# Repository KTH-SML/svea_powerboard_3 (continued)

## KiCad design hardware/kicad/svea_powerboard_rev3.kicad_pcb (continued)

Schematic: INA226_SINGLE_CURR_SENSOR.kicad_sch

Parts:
C89: 1u; C_0603_1608Metric; Manufacturer Part CL10B105KB8NQNC; LCSC Part Name 1uF ±10% 50V
C90: 100n; C_0603_1608Metric; Manufacturer Part CC0603KRX7R9BB104; LCSC Part Name 100nF ±10% 50V
NT18, NT19: NetTie_2; NetTie-2_SMD_Pad0.2mm
R2501: 100k; R_0402_1005Metric; LCSC C25741
U72: INA226AIDGSR; VSSOP-10_3x3mm_P0.5mm; Manufacturer Part INA226AIDGSR; LCSC Part Name 高侧/低侧测量双向电流/功率监视器，具有I2C兼容接口

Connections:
+3V3: C89.1, C90.2, R2501.2, U72.6 (VS+); also elsewhere on the board
/Battery System/ESC FET/OUT+: NT19.1; also elsewhere on the board
/Battery System/INA226_SINGLE_CURR_SENSOR_ESC/VIN_N: NT18.2, U72.9 (VIN-)
/Battery System/INA226_SINGLE_CURR_SENSOR_ESC/VIN_P: NT19.2, U72.8 (VBUS), U72.10 (VIN+)
Current/INA226-ESC-0x4E/ALERT: R2501.1, U72.3 (Alert); also elsewhere on the board
GND: C89.2, C90.1, U72.7 (GND); also elsewhere on the board
SCL_SLOW: U72.1 (A1), U72.5 (SCL); also elsewhere on the board
SDA_SLOW: U72.2 (A0), U72.4 (SDA); also elsewhere on the board
VCC_ESC: NT18.1; also elsewhere on the board

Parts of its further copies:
C126: 1u; C_0603_1608Metric; Manufacturer Part CL10B105KB8NQNC; LCSC Part Name 1uF ±10% 50V
C127: 100n; C_0603_1608Metric; Manufacturer Part CC0603KRX7R9BB104; LCSC Part Name 100nF ±10% 50V
NT28, NT29: NetTie_2; NetTie-2_SMD_Pad0.2mm
R3301: 100k; R_0402_1005Metric; LCSC C25741
U81: INA226AIDGSR; VSSOP-10_3x3mm_P0.5mm; Manufacturer Part INA226AIDGSR; LCSC Part Name 高侧/低侧测量双向电流/功率监视器，具有I2C兼容接口

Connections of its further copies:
+3V3: C126.1, C127.2, R3301.2, U81.6 (VS+); also elsewhere on the board
/Battery System/INA226_SINGLE_CURR_SENSOR_SERVO/VIN_N: NT28.2, U81.9 (VIN-)
/Battery System/INA226_SINGLE_CURR_SENSOR_SERVO/VIN_P: NT29.2, U81.8 (VBUS), U81.10 (VIN+)
/Battery System/servo_vcc: NT29.1; also elsewhere on the board
Current/INA226-SERVO-0x4F/ALERT: R3301.1, U81.3 (Alert); also elsewhere on the board
GND: C126.2, C127.1, U81.7 (GND); also elsewhere on the board
SCL_SLOW: U81.1 (A1), U81.2 (A0), U81.5 (SCL); also elsewhere on the board
SDA_SLOW: U81.4 (SDA); also elsewhere on the board
servo_vcc_indicator: NT28.1; also elsewhere on the board

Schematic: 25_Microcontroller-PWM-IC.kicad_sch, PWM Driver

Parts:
C117: 100n; C_0603_1608Metric; Manufacturer Part CC0603KRX7R9BB104; LCSC Part Name 100nF ±10% 50V
C118: 1u; C_0603_1608Metric; Manufacturer Part CL10A105KB8NNNC; LCSC Part Name 1uF ±10% 50V
R181, R182, R183, R184, R186, R188: 10k; R_0402_1005Metric; Manufacturer Part 0402WGF1002TCE; LCSC Part Name 10kΩ ±1% 62.5mW 厚膜电阻
U78: PCA9685PW,118; TSSOP-28_4.4x9.7mm_P0.65mm; Manufacturer Part PCA9685PW,118; LCSC Part Name 16通道、12位PWM Fm+ I2C总线LED控制器
U3201: EXB2HV102JV; Manufacturer Part EXB2HV102JV; LCSC C713453

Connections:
+3V3: C117.2, C118.2, R186.2, U78.24 (A5), U78.28 (VDD); also elsewhere on the board
/Battery System/ServoConnectors/Extra1: U3201.11; also elsewhere on the board
/Battery System/ServoConnectors/Extra2: U3201.10; also elsewhere on the board
/Battery System/ServoConnectors/FrontDiff: U3201.14; also elsewhere on the board
/Battery System/ServoConnectors/Gear: U3201.12; also elsewhere on the board
/Battery System/ServoConnectors/RearDiff: U3201.13; also elsewhere on the board
/Battery System/ServoConnectors/Steering: U3201.15; also elsewhere on the board
/Battery System/ServoConnectors/Throttle: U3201.16; also elsewhere on the board
GND: C117.1, C118.1, R181.1, R182.1, R183.1, R184.1, R188.2, U78.14 (VSS), U78.25 (EXTCLK); also elsewhere on the board
unnamed: R186.1, U78.1 (A0)
unnamed: R181.2, U78.2 (A1)
unnamed: R182.2, U78.3 (A2)
unnamed: R183.2, U78.4 (A3)
unnamed: R184.2, U78.5 (A4)
unnamed: U78.6 (LED0), U3201.1
unnamed: U78.7 (LED1), U3201.2
unnamed: U78.8 (LED2), U3201.3
unnamed: U78.9 (LED3), U3201.4
unnamed: U78.10 (LED4), U3201.5
unnamed: U78.11 (LED5), U3201.6
unnamed: U78.12 (LED6), U3201.7
unnamed: R188.1, U78.23 (OE#)
SCL_SLOW: U78.26 (SCL); also elsewhere on the board
SDA_SLOW: U78.27 (SDA); also elsewhere on the board

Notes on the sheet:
0x61

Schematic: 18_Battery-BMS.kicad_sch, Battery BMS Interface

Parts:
C114: 100n; C_0603_1608Metric; Manufacturer Part TCC0603X7R104K500CT; LCSC Part Name 100nF ±10% 50V
C115: 100p; C_0402_1005Metric; Manufacturer Part FCC0402N101J500AT; LCSC Part Name 100pF ±5% 50V
C116: 2.2u; C_0603_1608Metric; LCSC C23630
C119: 470n; C_0603_1608Metric; Manufacturer Part 0603B474K500NT; LCSC Part Name 470nF ±10% 50V
C120: 1u; C_0603_1608Metric; Manufacturer Part CGA0603X5R105K500JT; LCSC Part Name 1uF ±10% 50V
C3501, C3502, C3503, C3505: 220n; C_0402_1005Metric; lcsc C531424
C3504: 100p; C_0402_1005Metric; LCSC C281751
D21, D22: BAT46W-7-F; D_SOD-123; Manufacturer Part BAT46W-7-F; LCSC Part Name 电压:100V 电流:150mA
JP3401: SolderJumper_2_Open; SolderJumper-2_P1.3mm_Open_TrianglePad1.0x1.5mm
JP3402: SolderJumper_2_Bridged; SolderJumper-2_P1.3mm_Bridged_Pad1.0x1.5mm
LED9: XL-1608UOC-06; LED_0603_1608Metric; Manufacturer Part XL-1608UOC-06; LCSC C965800
Q3: L2N7002SLLT1G; SOT-23; Manufacturer Part L2N7002SLLT1G; LCSC Part Name 1个N沟道 耐压:60V 电流:380mA
R20: 220; R_0603_1608Metric; LCSC C22962
R21, R3506: 100k; R_0402_1005Metric; LCSC C25741
R175: 20; R_0603_1608Metric; Manufacturer Part FRC0603F20R0TS; LCSC Part Name 20Ω ±1% 100mW 厚膜电阻
R185, R187: 100; R_0603_1608Metric; Manufacturer Part 0603WAF1000T5E; LCSC Part Name 100Ω ±1% 100mW 厚膜电阻
R190: 100; R_1206_3216Metric; Manufacturer Part 1206W4F1000T5E; LCSC Part Name 100Ω ±1% 250mW 厚膜电阻
R3501, R3502, R3503: 20; R_0603_1608Metric; LCSC C22950
R3504, R3505, R3508: 10k; R_0402_1005Metric; LCSC C25744
R3507: 82k; R_0402_1005Metric; LCSC C4142
U80: BQ7694202pBR; TQFP-48_7x7mm_P0.5mm; Manufacturer Part BQ7694202PFBR; LCSC Part Name 适用于锂离子、锂聚合物和磷酸铁锂电池组的3节至10节高精度串联电池监控器和保护器

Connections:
/Battery System/Battery BMS Interface/ALERT_PULLUP: R20.1, R3508.2; also elsewhere on the board
/Battery System/Battery BMS Interface/BAL-CELL-2: R3502.1; also elsewhere on the board
/Battery System/Battery BMS Interface/BAL-CELL-TOP: JP3402.2 (B), R3501.1; also elsewhere on the board
/Battery System/Battery BMS Interface/BAL_CELL_BOT+: R3503.1; also elsewhere on the board
/Battery System/Battery BMS Interface/BAL_CELL_BOT-: R175.1; also elsewhere on the board
/Battery System/Battery BMS Interface/BQ-BAT: JP3401.1 (A); also elsewhere on the board
/Battery System/Battery BMS Interface/CHG: U80.45 (CHG); also elsewhere on the board
/Battery System/Battery BMS Interface/DSG: U80.43 (DSG); also elsewhere on the board
/Battery System/Battery BMS Interface/PCHG: U80.40 (PCHG)
/Battery System/Battery BMS Interface/PDSG: U80.39 (PDSG); also elsewhere on the board
/Battery System/Battery BMS Interface/REG18: C116.1, U80.24 (REG18); also elsewhere on the board
/Battery System/Battery BMS Interface/TS1: U80.21 (TS1)
/Battery System/Battery BMS Interface/TS2: U80.22 (TS2); also elsewhere on the board
/Battery System/Battery BMS Interface/TS3: U80.23 (TS3)
/Battery System/Battery BMS Interface/VC0: C3505.2, R175.2, U80.16 (VC0)
/Battery System/Battery BMS Interface/VC1: C3501.1, C3502.2, R3503.2, U80.15 (VC1)
/Battery System/Battery BMS Interface/VC3: C3502.1, C3503.2, R3502.2, U80.2 (VC9), U80.4 (VC8), U80.6 (VC7), U80.8 (VC6), U80.10 (VC5), U80.12 (VC4), U80.13 (VC3), U80.14 (VC2)
/Battery System/Battery BMS Interface/VC4: C3503.1, R3501.2, U80.48 (VC10)
/Battery System/Battery BMS Interface/VSS: C116.2, C120.1, C3501.2, C3504.2, C3505.1, R3506.2, R3507.2, U80.17 (VSS), U80.36 (REGIN), U80.37 (BREG); also elsewhere on the board
/Battery System/Battery Power Path/bat_shunt_N: R187.1; also elsewhere on the board
/Battery System/Battery Power Path/bat_shunt_P: R185.1; also elsewhere on the board
BQ/ALERT: Q3.1 (G), R21.1, R3508.1, U80.25 (ALERT)
BQ/ALERT/LED: LED9.2 (A), Q3.3 (D); also elsewhere on the board
BQ/RST-SHUT: R3506.1, U80.33 (RST_SHUT); also elsewhere on the board
GND: Q3.2 (S), R21.2; also elsewhere on the board
unnamed: D21.1, D22.1, R190.2
unnamed: D21.2, JP3401.2 (B)
unnamed: D22.2, JP3402.1 (A)
unnamed: LED9.1 (K), R20.2
unnamed: C119.2, C120.2, C3504.1, R190.1, U80.47 (BAT)
unnamed: C119.1, U80.46 (CP1)
unnamed: R3505.1, U80.41 (LD)
unnamed: R3504.1, U80.42 (PACK)
unnamed: R3507.1, U80.34 (REG2), U80.35 (REG1)
unnamed: C114.1, C115.2, R187.2, U80.20 (SRN)
unnamed: C114.2, C115.1, R185.2, U80.18 (SRP)
PACK+: R3504.2, R3505.2; also elsewhere on the board
SCL_SLOW: U80.26 (SCL); also elsewhere on the board
SDA_SLOW: U80.27 (SDA); also elsewhere on the board

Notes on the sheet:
4.5mA
0x08
Power from the big main bat connector
Everything here should be VSS

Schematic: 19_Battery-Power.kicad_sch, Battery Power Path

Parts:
C122, C123, C124, C125, C128, C129: 100n; C_0603_1608Metric; Manufacturer Part CL10B104KC8NNNC; LCSC Part Name 100nF ±10% 100V
D23, D28, D30: MMSZ5246B-7-F; D_SOD-123; Manufacturer Part MMSZ5246B-7-F; LCSC Part Name 独立式 耐压:16V 电流:0.1uA@12V
D24: MMSZ5267BT1G; D_SOD-123; Manufacturer Part MMSZ5267BT1G; LCSC Part Name 独立式 耐压:75V 电流:0.1uA@56V
D25, D27: BAT46W-7-F; D_SOD-123; Manufacturer Part BAT46W-7-F; LCSC Part Name 电压:100V 电流:150mA
D26: MMSZ5246B_R1_00001; D_SOD-123; Manufacturer Part MMSZ5246B_R1_00001; LCSC Part Name 独立式 耐压:16V 电流:0.1uA@12V
D29: BZT52C5V1S-7-F; D_SOD-323; Manufacturer Part BZT52C5V1S-7-F; LCSC Part Name 独立式 耐压:5.1V 电流:1uA
D31: BAT46W; D_SOD-123; Manufacturer Part BAT46W; LCSC Part Name 电压:100V 电流:150mA
NT30, NT31: NetTie_2; NetTie-2_SMD_Pad0.2mm
Q13, Q14: IPT012N08N5(TOKMAS); Infineon_PG-HSOF-8-1; Manufacturer Part IPT012N08N5(TOKMAS); LCSC Part Name 1个N沟道 耐压:85V 电流:300A
Q15: ZXMP10A17GTA; SOT-223; Manufacturer Part ZXMP10A17GTA; LCSC Part Name 1个P沟道 耐压:100V 电流:1.9A
Q16: BSS84AK,215; SOT-23; Manufacturer Part BSS84AK,215; LCSC Part Name 1个P沟道 耐压:50V 电流:180mA
Q17: BSS123NH6327; SOT-23; Manufacturer Part BSS123NH6327; LCSC Part Name 1个N沟道 耐压:100V 电流:0.19A
R196, R197: 100; R_0603_1608Metric; Manufacturer Part 0603WAF1000T5E; LCSC Part Name 100Ω ±1% 100mW 厚膜电阻
R198, R205, R210: 10M; R_0603_1608Metric; Manufacturer Part 0603WAF1005T5E; LCSC Part Name 10MΩ ±1% 100mW 厚膜电阻
R199, R203, R208: 47; R_0603_1608Metric; Manufacturer Part FRC0603J470 TS; LCSC Part Name 47Ω ±5% 100mW 厚膜电阻
R200: 1k; R_0603_1608Metric; Manufacturer Part FRC0603F1001TS; LCSC Part Name 1kΩ ±1% 100mW 厚膜电阻
R201: 68k; R_0603_1608Metric; Manufacturer Part RC0603FR-0768KL; LCSC Part Name 厚膜电阻 68kΩ ±1% 100mW
R202: 1M; R_0603_1608Metric; Manufacturer Part RC0603FR-071ML; LCSC Part Name 厚膜电阻 1MΩ ±1% 100mW
R204: 68k; R_0603_1608Metric; Manufacturer Part 0603WAF6802T5E; LCSC Part Name 68kΩ ±1% 100mW 厚膜电阻
R207: SEWF3920F1L00P9; Manufacturer Part SEWF3920F1L00P9; LCSC C5224161
R209: 470; R_0603_1608Metric; Manufacturer Part FRC0603J471 TS; LCSC Part Name 470Ω ±5% 100mW 厚膜电阻
R211: 10k; R_0603_1608Metric; Manufacturer Part 0603WAF1002T5E; LCSC Part Name 厚膜电阻 10kΩ ±1% 100mW
R3509: SMW_5W_47R_J; Manufacturer Part SMW 5W 47R J; LCSC C2937346

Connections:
/Battery System/Battery BMS Interface/BQ-BAT: C122.2, C124.1, D23.2 (A), Q13.2 (S), R198.1; also elsewhere on the board
/Battery System/Battery BMS Interface/CHG: R196.1; also elsewhere on the board
/Battery System/Battery BMS Interface/DSG: R197.1; also elsewhere on the board
/Battery System/Battery BMS Interface/PDSG: D24.1 (C), R201.1; also elsewhere on the board
/Battery System/Battery BMS Interface/VSS: D24.2 (A), D25.2; also elsewhere on the board
/Battery System/Battery Power Path/BAT-: C123.1, NT30.2, R207.1; also elsewhere on the board
/Battery System/Battery Power Path/DSG_G: D28.1 (C), D29.1 (C), Q16.2 (S), R203.2, R205.2, R209.1
/Battery System/Battery Power Path/bat_shunt_N: NT31.1; also elsewhere on the board
/Battery System/Battery Power Path/bat_shunt_P: NT30.1; also elsewhere on the board
CHARGE_DIRECT: D26.1, Q13.3 (D), Q14.3 (D), Q15.3 (S), R202.1; also elsewhere on the board
GND: C129.1, NT31.2, R207.2, R211.2; also elsewhere on the board
unnamed: C122.1, C123.2
unnamed: C124.2, C125.1
unnamed: C128.1, C129.2
unnamed: D23.1 (C), R196.2, R198.2, R199.1
unnamed: D25.1, R197.2, R200.1
unnamed: D27.2, R200.2, R204.1
unnamed: D27.1, D29.2 (A), Q16.1 (G), R204.2
unnamed: D30.1 (C), D31.2 (K), Q17.1 (G), R210.2
unnamed: D31.1 (A), R211.1
unnamed: Q13.1 (G), R199.2
unnamed: Q14.1 (G), R203.1
unnamed: Q15.2 (D), Q15.4 (D), R3509.1
unnamed: D26.2, Q15.1 (G), R201.2, R202.2
unnamed: Q16.3 (D), R208.2
unnamed: Q17.3 (D), R209.2
PACK+: C125.2, C128.2, D28.2 (A), D30.2 (A), Q14.2 (S), Q17.2 (S), R205.1, R208.1, R210.1, R3509.2; also elsewhere on the board

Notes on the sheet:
Local turn-off
Reverse polarity vcc protection
90A continous Kelvin connection

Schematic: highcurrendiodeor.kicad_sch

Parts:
C905: TCC1206X7R105M500HT; C_1206_3216Metric; LCSC Part C377070
C906, C907: C0603C104K5RACAUTO; C_0603_1608Metric; LCSC Part C129621
C908: CL32B475KBUYNNE; C_1210_3225Metric; Manufacturer Part CL32B475KBUYNNE; LCSC C170099
U902: MX5050D4005; TDSON-8-1; LCSC Part C41384467

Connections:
/Battery System/USBC_VCC: C905.2, C906.2, U902.1 (IN), U902.2 (IN), U902.3 (IN); also elsewhere on the board
GND: C905.1, C906.1, C907.1, C908.1, U902.4 (GND); also elsewhere on the board
USBC_OR_DC20: C907.2, C908.2, U902.5 (OUT); also elsewhere on the board

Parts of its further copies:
C701, C702, C901, C902, C1501, C1502, C1601, C1602: C0603C104K5RACAUTO; C_0603_1608Metric; LCSC Part C129621
C703, C903, C1503, C1603: TCC1206X7R105M500HT; C_1206_3216Metric; LCSC Part C377070
C704, C904, C1504, C1604: CL32B475KBUYNNE; C_1210_3225Metric; Manufacturer Part CL32B475KBUYNNE; LCSC C170099
U105, U701, U901, U1501: MX5050D4005; TDSON-8-1; LCSC Part C41384467

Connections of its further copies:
+12V: C1502.2, C1504.2, U1501.5 (OUT); also elsewhere on the board
/Battery System/12v_buck_out_net: C1501.2, C1503.2, U1501.1 (IN), U1501.2 (IN), U1501.3 (IN); also elsewhere on the board
/Battery System/Ideal_Diode_OR_SERVO/IN: C1601.2, C1603.2, U105.1 (IN), U105.2 (IN), U105.3 (IN); also elsewhere on the board
/Battery System/servo_vcc: C1602.2, C1604.2, U105.5 (OUT); also elsewhere on the board
GND: C701.1, C702.1, C703.1, C704.1, C901.1, C902.1, C903.1, C904.1, C1501.1, C1502.1, C1503.1, C1504.1, C1601.1, C1602.1, C1603.1, C1604.1, U105.4 (GND), U701.4 (GND), U901.4 (GND), U1501.4 (GND); also elsewhere on the board
IN-CHARGING-VCC-LIMITED: C701.2, C703.2, U701.1 (IN), U701.2 (IN), U701.3 (IN); also elsewhere on the board
PACK+: C901.2, C903.2, U901.1 (IN), U901.2 (IN), U901.3 (IN); also elsewhere on the board
VCC: C702.2, C704.2, C902.2, C904.2, U701.5 (OUT), U901.5 (OUT); also elsewhere on the board

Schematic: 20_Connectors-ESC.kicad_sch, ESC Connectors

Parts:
C87: 10u; C_0805_2012Metric; Manufacturer Part GRM21BR61H106KE43L; LCSC Part Name 10uF ±10% 50V
C88: 100n; C_0603_1608Metric; Manufacturer Part CC0603KRX7R9BB104; LCSC Part Name 100nF ±10% 50V
Q10: L2N7002SLLT1G; SOT-23; Manufacturer Part L2N7002SLLT1G; LCSC Part Name 1个N沟道 耐压:60V 电流:380mA
Q2401: SIRA99DP-T1-GE3; PowerPAK_SO-8_Single; lcsc C3289459
R148: 100k; R_0402_1005Metric; Manufacturer Part 0402WGF1003TCE; LCSC Part Name 100kΩ ±1% 62.5mW 厚膜电阻
R149: 47; R_0603_1608Metric; LCSC C23182
R150: 100k; R_0603_1608Metric; Manufacturer Part FRC0603J104 TS; LCSC Part Name 100kΩ ±5% 100mW 厚膜电阻
ZD1: BZT52C12_C43491; Manufacturer Part BZT52C12; LCSC C43491

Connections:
/Battery System/ESC FET/OUT+: Q2401.5 (D); also elsewhere on the board
ESC/EN: Q10.1 (G), R150.1; also elsewhere on the board
GND: C87.1, C88.1, Q10.2 (S), R150.2; also elsewhere on the board
unnamed: Q10.3 (D), R149.2
unnamed: Q2401.4 (G), R148.1, R149.1, ZD1.2 (A)
PACK+: C87.2, C88.2, Q2401.1 (S), Q2401.2 (S), Q2401.3 (S), R148.2, ZD1.1 (K); also elsewhere on the board

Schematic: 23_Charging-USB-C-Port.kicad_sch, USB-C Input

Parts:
C76: 1u; C_0603_1608Metric; Manufacturer Part CGA0603X5R105K500JT; LCSC Part Name 1uF ±10% 50V
C2001: 1u; C_0603_1608Metric; LCSC C5199872
D16: TPD4E02B04DQAR; USON-10_L2.5-W1.0-P0.50-BL; Manufacturer Part TPD4E02B04DQAR; LCSC Part Name 双向ESD
D18: BZT52C15; D_SOD-123; Manufacturer Part BZT52C15; LCSC Part Name BZT52C15
D34: SMF24A_C19077514; SOD-123FL_L2.8-W1.8-LS3.6-RD; Manufacturer Part SMF24A; LCSC C19077514
JP2001, JP2002, JP2005, JP2006: SolderJumper_2_Open; SolderJumper-2_P1.3mm_Open_TrianglePad1.0x1.5mm
JP2003, JP2004: SolderJumper_2_Bridged; SolderJumper-2_P1.3mm_Bridged_Pad1.0x1.5mm
NT2001: NetTie_2; NetTie-2_SMD_Pad0.2mm
Q9: DMP3028LK3-13; TO-252-2; Manufacturer Part DMP3028LK3-13; LCSC Part Name 1个P沟道 耐压:30V 电流:27A
R2001, R2003, R2011: 909k; R_0402_1005Metric; LCSC C25799
R2002, R2004: 100k; R_0402_1005Metric; LCSC C25741
R2005: 10; R_0402_1005Metric; LCSC C2906862
R2006: 30k; R_0402_1005Metric; LCSC C2909347
R2008: 10k; R_0402_1005Metric; LCSC C25744
R2009: 19.1k; R_0603_1608Metric; LCSC C2960926
R2010: 21k; R_0603_1608Metric; LCSC C22956
U65: HUSB238A-BB001-QN16R; QFN-16_L3.0-W3.0-P0.50-BL-EP1.7; Manufacturer Part HUSB238A-BB001-QN16R; LCSC Part Name HUSB238A-BB001-QN16R
USB2: TYPE-C-31-M-12; Manufacturer Part TYPE-C-31-M-12; LCSC C165948
USBC1: TYPE-C-31-M-12; USB-C_SMD-TYPE-C-31-M-12; Manufacturer Part TYPE-C-31-M-12; LCSC Part Name Type-C 母; not fitted

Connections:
+3V3: R2008.1; also elsewhere on the board
/Battery System/USB-C Input/cc1: D16.5 (IO4), D16.6 (NC), U65.3 (CC1), USB2.A5 (CC1), USBC1.A5 (CC1)
/Battery System/USB-C Input/cc2: D16.1 (IO1), D16.10 (NC), U65.4 (CC2), USB2.B5 (CC2), USBC1.B5 (CC2)
/Battery System/USB-C Input/dn: D16.2 (IO2), D16.9 (NC), U65.2 (D-), USB2.A7 (DN1), USB2.B7 (DN2), USBC1.A7 (DN1), USBC1.B7 (DN2)
/Battery System/USB-C Input/dp: D16.4 (IO3), D16.7 (NC), U65.1 (D+), USB2.A6 (DP1), USB2.B6 (DP2), USBC1.A6 (DP1), USBC1.B6 (DP2)
/Battery System/USB-C Input/usbc_vbus: C76.2, D18.1 (K), D34.1 (K), Q9.3 (S), R2002.2, R2005.2, R2011.1, U65.16 (VBUS), USB2.A4B9 (VBUS), USB2.B4A9 (VBUS), USBC1.A4 (VBUS), USBC1.A9 (VBUS), USBC1.B4 (VBUS), USBC1.B9 (VBUS)
/Battery System/USBC_VCC: Q9.2 (D); also elsewhere on the board
GND: C76.1, C2001.2, D16.3 (GND), D16.8 (GND), D34.2 (A), JP2006.2 (B), NT2001.1, U65.17 (GND), USB2.1 (EH), USB2.2 (EH), USB2.3 (EH), USB2.4 (EH), USB2.A1B12 (GND), USB2.B1A12 (GND), USBC1.A1 (GND), USBC1.A12 (GND); also elsewhere on the board
unnamed: D18.2 (A), Q9.1 (G), R2002.1, R2006.2
unnamed: JP2001.2 (B), JP2003.2 (B), U65.10 (SCL/SNK_ISET)
unnamed: JP2002.2 (B), JP2004.2 (B), U65.9 (SDA/SNK_VSET)
unnamed: JP2003.1 (A), R2010.1
unnamed: JP2004.1 (A), R2009.1
unnamed: JP2005.1 (A), U65.8 (ADDR/ORIENT)
unnamed: JP2005.2 (B), R2011.2
unnamed: JP2006.1 (A), R2006.1, U65.15 (GATE)
unnamed: NT2001.2, R2003.2, R2004.2, R2009.2, R2010.2
unnamed: R2003.1, U65.6 (DBG_N)
unnamed: R2001.2, U65.7 (EN_HVDCP/OUT1)
unnamed: C2001.1, R2001.1, R2005.1, U65.5 (VDD)
unnamed: USBC1.B1 (GND), USBC1.B12 (GND)
SCL_SLOW: JP2001.1 (A); also elsewhere on the board
SDA_SLOW: JP2002.1 (A); also elsewhere on the board
USB-C/HUSB238A/EN#: R2004.1, U65.12 (EN_N); also elsewhere on the board
USB-C/HUSB238A/FAULT-OUT2: U65.13 (FAULT/OUT2); also elsewhere on the board
USB-C/HUSB238A/INT: R2008.2, U65.11 (INT_N); also elsewhere on the board

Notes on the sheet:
Make sure no significant current is pulled until about 20V
3.25A 20V Higher requires i2c

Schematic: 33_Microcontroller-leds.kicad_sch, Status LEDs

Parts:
C83, C84: 100n; C_0603_1608Metric; Manufacturer Part CC0603KRX7R9BB104; LCSC Part Name 100nF ±10% 50V
C2301: 189RV0019; Manufacturer Part 189RV0019; LCSC C7471881
CN2301: S4B-XH-A_LF_SN; Manufacturer Part S4B-XH-A(LF)(SN); LCSC C157925
JP1: Jumper_2_Small_Bridged; SolderJumper-2_P1.3mm_Bridged_RoundedPad1.0x1.5mm
R11: 62; R_0402_1005Metric
U2: SN74LVC1G17DBVR; SOT-23-5; MPN SN74LVC1G17DBVR(AT); LCSC Part C55089942
U70: WS2815F; LED_WS2812_PLCC6_5.0x5.0mm_P1.6mm; Manufacturer Part WS2815F; LCSC Part Name SMD灯珠,RGB三色

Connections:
+5V: C83.2, U2.5 (VCC); also elsewhere on the board
+12V: C84.2, C2301.1, CN2301.1, U70.2 (VDD); also elsewhere on the board
GND: C83.1, C84.1, C2301.2, CN2301.4, JP1.1 (A), U2.3 (GND), U70.5 (GND), U70.6 (DIN2); also elsewhere on the board
LED/WS2815/DATA: U2.2 (A); also elsewhere on the board
unnamed: CN2301.2, JP1.2 (B)
unnamed: R11.1, U2.4 (Y)
unnamed: R11.2, U70.4 (DIN1)
unnamed: CN2301.3, U70.3 (DO)

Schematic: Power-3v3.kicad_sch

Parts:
C2601: TAJA106K016RNJ; Manufacturer Part TAJA106K016RNJ; LCSC C7171
C2602: CL21A106KAYNNNE; Manufacturer Part CL21A106KAYNNNE; LCSC C15850
U2601: AMS1117-3_3_C347222; SOT-223; Manufacturer Part AMS1117-3.3; LCSC C347222

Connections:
/Battery System/3v3 rail/3v3_out: C2601.1, U2601.2 (VOUT(TAB)); also elsewhere on the board
/Battery System/5v rail/5V buck rail: C2602.1, U2601.3 (VIN); also elsewhere on the board
GND: C2601.2, C2602.2, U2601.1 (ADJ(GND)); also elsewhere on the board

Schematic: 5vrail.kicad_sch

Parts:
C96: 100n; C_0603_1608Metric; Manufacturer Part CC0603KRX7R9BB104; LCSC Part Name 100nF ±10% 50V
C98: 47uF; CAP-SMD_BD6.3-L6.6-W6.6-LS7.6-FD; Manufacturer Part RVT1H470M0607; LCSC Part Name 47uF ±20% 50V
C99: 1u; C_0603_1608Metric; Manufacturer Part CL10A105KB8NNNC; LCSC Part Name 1uF ±10% 50V
C2701, C2702: CL32B475KBUYNNE; Manufacturer Part CL32B475KBUYNNE; LCSC C170099
C2703, C2704: CL32B226KAJNNNE; Manufacturer Part CL32B226KAJNNNE; LCSC C309062
C2705: 22p; C_0402_1005Metric_Pad0.74x0.62mm_HandSolder; not fitted
NT2701: NetTie_2; NetTie-2_SMD_Pad0.3mm
Q12: L2N7002SLLT1G; SOT-23; Manufacturer Part L2N7002SLLT1G; LCSC Part Name 1个N沟道 耐压:60V 电流:380mA
R2701: 40.2k; R_0402_1005Metric; LCSC C2933097
R2702: 10k; R_0402_1005Metric; LCSC C25744
R2703: 15.8k; R_0402_1005Metric; LCSC C26956
R2704, R2705, R2706: 100k; R_0402_1005Metric; LCSC C25741
U2701: TPSM33625RDNR; QFN-11_L4.5-W3.5-P0.50-TL_TPSM365R6FRDNR; Manufacturer Part TPSM33625RDNR; LCSC C7073593

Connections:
+3V3: R2706.2; also elsewhere on the board
/Battery System/5v rail/5V buck rail: C2703.2, C2704.2, NT2701.2, U2701.4 (VOUT); also elsewhere on the board
/Battery System/danger_rail: C96.2, C98.1, C2701.1, C2702.1, R2704.1, U2701.3 (VIN); also elsewhere on the board
GND: C96.1, C98.2, C99.1, C2701.2, C2702.2, C2703.1, C2704.1, Q12.2 (S), R2702.2, R2703.2, R2705.1, U2701.10 (GND); also elsewhere on the board
unnamed: C2705.1, NT2701.1, R2701.1
unnamed: Q12.3 (D), R2704.2, U2701.2 (EN)
unnamed: C2705.2, R2701.2, R2702.1, U2701.9 (FB)
unnamed: R2703.1, U2701.11 (RT)
unnamed: C99.2, U2701.8 (VCC)
Power/5V-Buck/EN#: Q12.1 (G), R2705.2; also elsewhere on the board
Power/5V-Buck/PGOOD: R2706.1, U2701.1 (PGOOD); also elsewhere on the board

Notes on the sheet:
2.5A variant

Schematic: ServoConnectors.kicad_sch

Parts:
C10, C11, C12, C2101: HGC1206R5107M100NSPJ; Manufacturer Part HGC1206R5107M100NSPJ; LCSC C7432784
H3, H4: TSW-104-08-T-T-RA; HDR-TH_12P-P2.54-H-M-R3-C4_TSW-104-08-XXX-T-RA; Manufacturer Part TSW-104-08-T-T-RA; LCSC Part Name 间距:2.54mm 方针 弯插
JP2102: SolderJumper_2_Open; SolderJumper-2_P1.3mm_Open_TrianglePad1.0x1.5mm

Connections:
/Battery System/ServoConnectors/3v3: H3.2; also elsewhere on the board
/Battery System/ServoConnectors/Extra1: H4.6; also elsewhere on the board
/Battery System/ServoConnectors/Extra2: H4.9; also elsewhere on the board
/Battery System/ServoConnectors/FrontDiff: H3.9; also elsewhere on the board
/Battery System/ServoConnectors/Gear: H4.3; also elsewhere on the board
/Battery System/ServoConnectors/RearDiff: H3.12; also elsewhere on the board
/Battery System/ServoConnectors/Steering: H4.12; also elsewhere on the board
/Battery System/ServoConnectors/Throttle: H3.6; also elsewhere on the board
GND: C10.1, C11.1, C12.1, C2101.1, H3.1, H3.4, H3.7, H3.10, H4.1, H4.4, H4.7, H4.10; also elsewhere on the board
unnamed: H3.5, JP2102.1 (A)
SBUS_RECEIVER: H3.3; also elsewhere on the board
servo_vcc_indicator: C10.2, C11.2, C12.2, C2101.2, H3.8, H3.11, H4.2, H4.5, H4.8, H4.11, JP2102.2 (B); also elsewhere on the board

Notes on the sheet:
Add jumper to use esc supply not included due to space and can just solder em together if needed

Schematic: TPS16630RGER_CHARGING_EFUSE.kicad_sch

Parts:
C16: 1u; C_0603_1608Metric; Manufacturer Part CL10B105KB8NQNC; LCSC Part Name 1uF ±10% 50V
C74: 100n; C_0603_1608Metric; Manufacturer Part CC0603KRX7R9BB104; LCSC Part Name 100nF ±10% 50V
C75: 22n; C_0603_1608Metric; Manufacturer Part TCC0603X7R223M500CT; LCSC Part Name 22nF ±20% 50V
D17, D36: SMBJ24A_C224017; D_SMB; Manufacturer Part SMBJ24A; LCSC C224017
D35: SS54_C123946; D_SMA; Manufacturer Part SS54; LCSC C123946
JP1902: SolderJumper_2_Open; SolderJumper-2_P1.3mm_Open_TrianglePad1.0x1.5mm
R1901, R1907: 100k; R_0402_1005Metric; LCSC C25741
R1902: 3.92k; R_0402_1005Metric; LCSC C2960797
R1903: 1.58k; R_0402_1005Metric; LCSC C2974011
R1904: 442k; R_0402_1005Metric; LCSC C49654384
R1905: 11k; R_0402_1005Metric; LCSC C2909313
R1906: 20k; R_0402_1005Metric; LCSC C25765
R1908: 19.1k; R_0402_1005Metric; LCSC C2998158
U62: TPS16630RGER; Manufacturer Part TPS16630RGER; LCSC Part Name 具有可调节输出功率限制功能的60V、6A电子保险丝

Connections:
+3V3: R1901.1, R1907.2; also elsewhere on the board
GND: C16.2, C74.1, C75.1, D17.2, D35.2 (A), D36.2, JP1902.1 (A), R1903.1, R1906.1, R1908.1, U62.8 (GND), U62.11 (MODE), U62.20 (N.C), U62.21 (N.C), U62.22 (N.C), U62.23 (N.C), U62.25 (EP); also elsewhere on the board
IN-CHARGING-VCC-LIMITED: D17.1, D35.1 (K), U62.17 (OUT), U62.18 (OUT), U62.19 (N.C); also elsewhere on the board
unnamed: JP1902.2 (B), R1902.1, R1903.2
unnamed: R1902.2, U62.10 (ILIM)
unnamed: R1905.1, R1906.2, U62.7 (OVP)
unnamed: R1904.1, R1905.2, U62.6 (UVLO)
unnamed: C75.2, U62.9 (dVdT)
USBC_OR_DC20: C16.1, C74.2, D36.1, R1904.2, U62.1 (IN), U62.2 (IN), U62.5 (P_IN), U62.24 (N.C); also elsewhere on the board
eFuse/TPS16630/FAULT: R1907.1, U62.14 (FLT#); also elsewhere on the board
eFuse/TPS16630/IMON: R1908.2, U62.13 (IMON); also elsewhere on the board
eFuse/TPS16630/PGOOD: U62.16 (PGOOD); also elsewhere on the board
eFuse/TPS16630/SHDN: R1901.2, U62.12 (SHDN#); also elsewhere on the board

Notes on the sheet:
Active High. A high indicates that the internal FET is enhanced.
Solder for 4.59A, 92W Worst case 4.95A Default limit 3.25 nominal like for 60W charger
analog current monitor output
should make it passively prevent overloading the usb c while its ramping
open-drain fault
approx 9ms

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
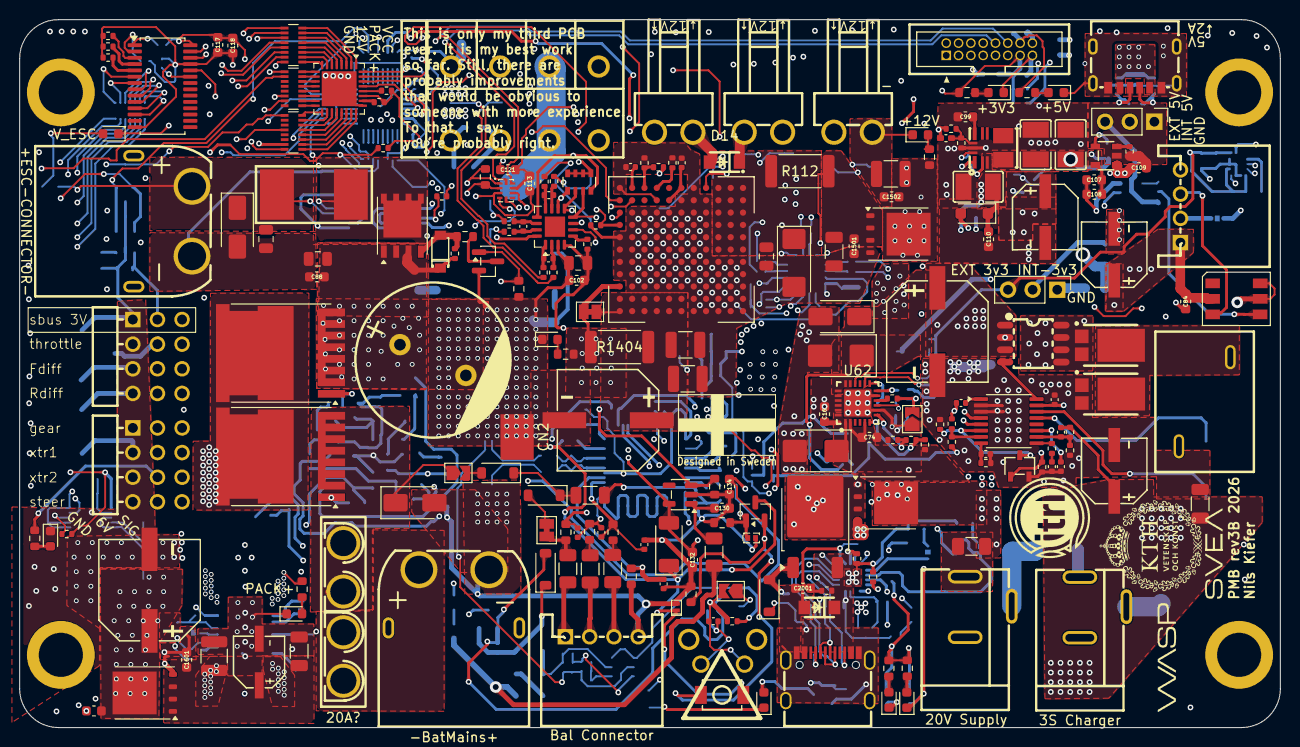
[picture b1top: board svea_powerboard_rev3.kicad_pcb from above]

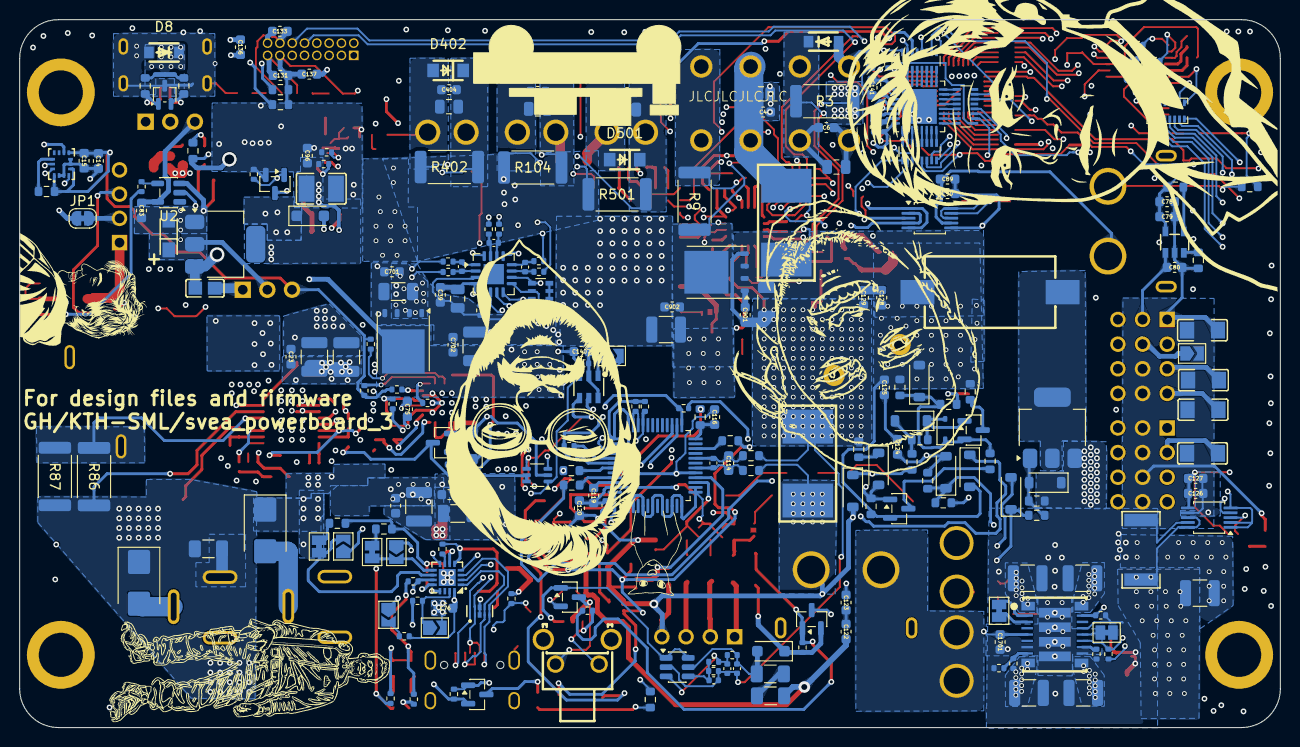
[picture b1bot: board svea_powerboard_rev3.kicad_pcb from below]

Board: 8 copper layers, 130.0 x 73.0 mm, 469 parts (254 on the bottom side), 319 nets.

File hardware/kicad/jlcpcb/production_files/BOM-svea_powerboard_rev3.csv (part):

Comment,Designator,Footprint,LCSC,Quantity
0440007_WR,"U10,U101",Fuse_1206_3216Metric,C206973,2
0466001.NRHF,"F2,F3,F3601,F4",Fuse_1206_3216Metric,C151135,4
1.58k,R1903,R_0402_1005Metric,C2974011,1
10,"R100,R101,R102,R160,R161,R163,R164,R165,R166,R96,R97,R99",R_0402_1005Metric,C25077,12
10,R2005,R_0402_1005Metric,C2906862,1
100,R190,R_1206_3216Metric,C17901,1
100,"R109,R185,R187,R196,R197",R_0603_1608Metric,C22775,5
100k,"R107,R1401,R1402,R148,R1702,R1705,R1901,R1907,R2002,R2004,R21,R2501,R2704,R2705,R2706,R3301,R3506,R3601,R3603,R604,R606,R610",R_0402_1005Metric,C25741,22
100k,"R145,R150,R168,R213,R214",R_0603_1608Metric,C25803,5
100n,"C102,C105,C106,C107,C109,C110,C112,C113,C114,C117,C122,C123,C124,C125,C127,C128,C129,C134,C14,C141,C142,C1701,C23,C39,C4,C404,C47,C502,C6,C74,C78,C80,C83,C84,C88,C90,C96",C_0603_1608Metric,C14663,37
100n,"C1405,C1406,C3601,C3602,C3603,C3604,C605,C606,C608",C_0402_1005Metric,C307331,9
100p,"C115,C3504",C_0402_1005Metric,C281751,2
100u,C68,CAP-SMD_BD5.0-L5.3-W5.3-LS6.3-FD,C72473,1
105k,R607,R_0402_1005Metric,C2933067,1
10M,"R198,R205,R210",R_0603_1608Metric,C7250,3
10k,"RN1,RN2",R_Array_Convex_4x0603,C102646,2
10k,"R162,R181,R182,R183,R184,R186,R188,R19,R2008,R241,R242,R243,R268,R269,R2702,R3504,R3505,R3508,R3609,R3610,R603,R609,R74,R98",R_0402_1005Metric,C25744,24
10k,"R17,R211",R_0603_1608Metric,C25804,2
10n,"C1001,C1002,C1003,C2801,C2802,C2803",C_0402_1005Metric,C15195,6
10u,"C121,C136,C137",C_0603_1608Metric,C237435,3
10u,"C103,C2401,C3,C40,C403,C46,C5,C501,C87",C_0805_2012Metric,C440198,9
10u,"C65,C66",C_1210_3225Metric,C77102,2
10u,C601,C_1206_3216Metric,C89632,1
11.3k,R15,R_0603_1608Metric,C22860,1
11k,"R1403,R1905",R_0402_1005Metric,C2909313,2
120,R602,R_0402_1005Metric,C25079,1
15.8k,R2703,R_0402_1005Metric,C26956,1
150,R5,R_0603_1608Metric,C22808,1
16m,"R104,R3,R402,R501,R9",R_2512_6332Metric,C5775686,5
1825027-8,SW3601,1825027-8,C266196,1
189RV0019,C2301,189RV0019,C7471881,1
19-217UYOC/S3112/TR8,LED7,LED_0603_1608Metric,C264473,1
19.1k,R2009,R_0603_1608Metric,C2960926,1
19.1k,R1908,R_0402_1005Metric,C2998158,1
1M,R202,R_0603_1608Metric,C22935,1
1M,R601,R_0402_1005Metric,C26083,1
1k,R3602,R_0402_1005Metric,C11702,1
1k,"R200,R77,R79",R_0603_1608Metric,C21190,3
1k,"R4,R8",R_0603_1608Metric,C2907002,2
1m,"R18,R189",R3920,C5224154,2
1u,"C101,C111,C118,C120,C126,C130,C132,C135,C1407,C15,C16,C2001,C76,C89,C99",C_0603_1608Metric,C5199872,15
2.2k,"R105,R118",R_0603_1608Metric,C4190,2
2.2u,C116,C_0603_1608Metric,C23630,1
20,"R175,R3501,R3502,R3503",R_0603_1608Metric,C22950,4
20k,"R1704,R1906",R_0402_1005Metric,C25765,2
21.5k,"R113,R114",R_0402_1005Metric,C2933081,2
21k,R2010,R_0603_1608Metric,C22956,1
220,"R147,R20",R_0603_1608Metric,C22962,2
220n,"C3501,C3502,C3503,C3505",C_0402_1005Metric,C531424,4
220n,"C1404,C604",C_0402_1005Metric,C694490,2
22k,"R13,R14",R_0603_1608Metric,C31850,2
22n,C75,C_0603_1608Metric,C21122,1
22u,"C20,C21",C_1210_3225Metric,C778721,2
22u,"C108,C79",C_0603_1608Metric,C86295,2
232k,R3612,R_0402_1005Metric,C27000,1
24.9k,R608,R_0402_1005Metric,C138027,1
26.7k,R1703,R_0402_1005Metric,C5121521,1
2p,C607,C_0402_1005Metric,C1558,1
3.4K,R103,R_0402_1005Metric,C4940,1
3.92k,R1902,R_0402_1005Metric,C2960797,1
309k,R3611,R_0402_1005Metric,C122546,1
30k,R2006,R_0402_1005Metric,C2909347,1
36.5k,R1405,R_0402_1005Metric,C25887,1
4.02k,R7,R_0603_1608Metric,C23040,1
4.7k,"R106,R108,R2,R212",R_0603_1608Metric,C23162,4
40.2k,R2701,R_0402_1005Metric,C2933097,1
442k,R1904,R_0402_1005Metric,C49654384,1
47,"R149,R199,R203,R208",R_0603_1608Metric,C23182,4
470,R209,R_0603_1608Metric,C23179,1
4700u,C104,35PX4700MEFC16X35_5,C1600541,1
470n,"C119,C131,C133",C_0603_1608Metric,C77572,3
470p,C603,C_0402_1005Metric,C1537,1
47k,R1701,R_0402_1005Metric,C25792,1
47uF,C98,CAP-SMD_BD6.3-L6.6-W6.6-LS7.6-FD,C72523,1
5.1k,"R215,R216",R_0603_1608Metric,C23186,2
5.76k,R605,R_0402_1005Metric,C5153969,1
60m,R86,R_2512_6332Metric,C875732,1
68k,"R201,R204",R_0603_1608Metric,C23231,2
"74AHCT1G125GW,125-JSM",U69,SOT-353_SC-70-5,C53114384,1
7m,"R112,R1404",R_2512_6332Metric,C49164689,2
82k,R3507,R_0402_1005Metric,C4142,1
909k,"R2001,R2003,R2011",R_0402_1005Metric,C25799,3
ADS1115IRUGT,U104,ADS1115IRUGT,C701611,1
AMS1117-3_3_C347222,U2601,SOT-223,C347222,1
AO4459,Q602,AO4459,C49047,1
BAT46W,D31,D_SOD-123,C7420332,1
BAT46W-7-F,"D21,D22,D25,D27,D3601",D_SOD-123,C83152,5
BQ7694202pBR,U80,TQFP-48_7x7mm_P0.5mm,C3682863,1
BSS123NH6327,Q17,SOT-23,C5205497,1
"BSS84AK,215",Q16,SOT-23,C127273,1
BZT52C12_C43491,ZD1,BZT52C12_C43491,C43491,1
BZT52C15,"D18,D3602",D_SOD-123,C173427,2
BZT52C3V3-E3-18,D601,D_SOD-123F,C5224067,1
BZT52C5V1S-7-F,D29,D_SOD-323,C151348,1
C0603C104K5RACAUTO,"C1501,C1502,C1601,C1602,C1801,C1802,C701,C702,C801,C802,C901,C902",C_0603_1608Metric,C129621,12
C238129,CN2,5016,C238129,1
CL21A106KAYNNNE,C2602,CL21A106KAYNNNE,C15850,1
CL21A226MAYNNNE,C1409,C_0805_2012Metric,C602037,1
CL32B226KAJNNNE,"C2703,C2704",CL32B226KAJNNNE,C309062,2
CL32B475KBUYNNE,"C1401,C1403,C1504,C1604,C1804,C2701,C2702,C704,C804,C904",C_1210_3225Metric,C170099,10
CN3722,U30,TSSOP-16_4.4x5mm_P0.65mm,C77905,1
DB142R-5_08-4P,CN101,DB142R-5_08-4P,C2898711,1
DC-S009A-D025-7A,"DC101,DC102",DC-S009A-D025-7A,C7544903,2
DEP1016NP-220PB,L602,DEP1016NP-220PB,C2897825,1
DMP3028LK3-13,Q9,TO-252-2,C461078,1
ESD9X5VU,D33,ESD9X5VU,C2875160,1
EXB2HV102JV,"U301,U302,U303,U3201,U3401,U3402,U3403",R_Array_Convex_8x0602,C713453,7
GRM32ER71A476ME15L,"C1702,C1703,C1704",C_1210_3225Metric,C415541,3
HGC1206R5107M100NSPJ,"C10,C11,C12,C2101",HGC1206R5107M100NSPJ,C7432784,4
HUSB238A-BB001-QN16R,U65,QFN-16_L3.0-W3.0-P0.50-BL-EP1.7,C24833806,1
INA226AIDGSR,"U72,U81",VSSOP-10_3x3mm_P0.5mm,C49851,2
INA3221AIRGVR,"CUR_1,CUR_2",Texas_RGV0016A_VQFN-16-1EP_4x4mm_P0.65mm_EP2.1x2.1mm,C181255,2
IPT012N08N5(TOKMAS),"Q13,Q14",Infineon_PG-HSOF-8-1,C19626224,2
JK-nSMD050-30,"F3602,F5",Fuse_1206_3216Metric,C720075,2
L2N7002SLLT1G,"Q1,Q10,Q12,Q18,Q3,Q3602,Q601",L2N7002SLLT1G,C22446827,7
LSM6DSOXTR,U1,LGA-14L_L3.0-W2.5-P0.50-TL,C481766,1
LTM8055IY_PBF,U47,BGA121C127P11X11_1500X1500X512N,C690729,1
MCP4725A0T-E/CH,U44,SOT-23-6_L2.9-W1.6-P0.95-LS2.8-BL,C144198,1
MMSZ5246B-7-F,"D23,D28,D30",D_SOD-123,C74710,3
MMSZ5246B_R1_00001,D26,D_SOD-123,C282317,1
MMSZ5267BT1G,D24,D_SOD-123,C80160,1
MT9700-N,"U67,U76",SOT-23-5_L2.9-W1.6-P0.95-LS2.9-BL,C42441843,2
MX5050D4005,"U105,U1501,U1801,U701,U801,U901",TDSON-8-1,C41384467,6
NCP718ASN330T1G,U82,TSOT-23-5,C603785,1
"PCA9685PW,118",U78,TSSOP-28_4.4x9.7mm_P0.65mm,C2678753,1
PCAL6524HEAZ,"U304,U3404",LFCSP-32-1EP_5x5mm_P0.5mm_EP3.6x3.6mm,C3000497,2
PINHD_1x3_Male,"J101,J103",PinHeader_1x03_P2.54mm_Vertical,C42431836,2
PMEG10030ELPX,U84,D_SOD-128,C5260346,1
PSC-1608U50GC-G4,LED6,LED_0603_1608Metric,C22371298,1
RLM25FEER005,R16,RLM25FEER005,C185817,1
RVT1H220M0605,C32,RVT1H220M0605,C72505,1
S4B-XH-A_LF_SN,"CN102,CN2301",S4B-XH-A_LF_SN,C157925,2
SBR8U60P5-13,"D11,D12",POWERDI-5_L5.4-W4.0-LS6.5-RD,C154726,2
SEWF3920F1L00P9,R207,SEWF3920F1L00P9,C5224161,1
SI2309A,Q3603,SOT-23,C2681220,1
SIRA99DP-T1-GE3,Q2401,PowerPAK_SO-8_Single,C3289459,1
SMAJ16A,"D1,D10",D_SMA,C908770,2
SMBJ24A_C224017,"D101,D102,D17,D36",D_SMB,C224017,4
SMF13A,"D14,D3,D402,D501",SOD-123FL_L2.8-W1.8-LS3.6-RD,C353315,4
SMF24A_C19077514,D34,SOD-123FL_L2.8-W1.8-LS3.6-RD,C19077514,1
SMF5_0A_C2857263,D8,SOD-123F_L2.8-W1.8-LS3.7-RD,C2857263,1
SMW_5W_47R_J,R3509,SMW_5W_47R_J,C2937346,1
SS54_C123946,D35,D_SMA,C123946,1
TAJA106K016RNJ,C2601,TAJA106K016RNJ,C7171,1
TCC1206X7R105M500HT,"C1503,C1603,C1803,C703,C803,C903",C_1206_3216Metric,C377070,6
TI TPL0401B-10DCKR,U601,Texas_R-PDSO-G6,C2666599,1
TPD2E2U06DCKR,D9,SOT-323_SC-70,C1855726,1
TPD4E02B04DQAR,D16,USON-10_L2.5-W1.0-P0.50-BL,C106794,1
TPS16630RGER,U62,TPS16630RGER,C1850279,1
TPS2121RUXR,"U102,U103",TPS2121RUXR,C485916,2
TPS3700DDCR,U3601,SOT-23-6,C33002,1
TPSC686M016R0200,C1408,CP_EIA-6032-28_Kemet-C,C444808,1
TPSM33625RDNR,U2701,QFN-11_L4.5-W3.5-P0.50-TL_TPSM365R6FRDNR,C7073593,1
TPSM63610RDFR,U55,TPSM63610RDFR,C7125816,1
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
